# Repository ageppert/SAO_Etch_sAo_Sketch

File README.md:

# Etch sAo Sketch

The perfect pairing of an OLED Display, analog potentiometers, and a 3-axis accelerometer!

This is the primary repository for all things relevant to the Etch sAo Sketch.

Learn more about this project at: https://hackaday.io/project/197581-etch-sao-sketch

If you use the Arduino Demo code make sure it is configured for your hardware version (HWV) of the Etch sAo Sketch.

IMPORTANT ERRATA APPLIES TO ALL VERSIONS:

There is too much combined pull-up resistance with this board, the OLED board, the Hackaday Badge, and the Pico. This inhibits some I2C hardware implementations from working with the OLED display.

SOLUTION A: Firmware workaround is to use software I2C. See: https://github.com/ageppert/SAO_Etch_sAo_Sketch/pull/1

SOLUTION B: Hardware mods to remove interfering components. See: https://github.com/ageppert/SAO_Etch_sAo_Sketch/issues/8

-------------

# V1.3 - OLED VERSION - Hackaday Europe 2025 Elecrow version

This version was manufactured for Hackaday Europe 2025 by Elecrow and includes the Elecrow logo on the PCB below the screen. The files have been copied into this repository for easy reference, although it was in a more generic "SAO Sketch" repo for production. Hopefully you got a sticker from one of us to upgrade your SAO to "Etch sAo Sketch" when we were together in Berlin!

V1.3.1 FIXES: Removed I2C Pull-up Resistors R1/2 from the board.

-------------

# V1.2 - OLED VERSION - NOT BUILT

This version was an un-fabricated step in the development for Hackaday Europe 2025 with a separate repository located here: https://github.com/ageppert/SAO_Sketch. This version builds on V1.1 with some clean-up in the schematic and layout.

-------------

# V1.1 - OLED VERSION - Small batch to sell on Tindie

Refinements include:
1) Enable full range of the analog pots via the accelerometer's [reduced range] ADC inputs, with the option to still use analog signals on GPIO 1 and 2.
2) Use a taller male SAO header for easier connection to the main (red) PCBA.
3) Tweak alignment hole size/position for the alignment spheres and OLED position.

V1.1.1 FIXES: Removed I2C Pull-up Resistors R1/2 from the board.

Otherwise, it looks and functions just like V1.0.

-------------

# V1.0 - OLED VERSION - Shared at Hackaday Supercon.8 in 2024 and on Tindie

This version was shared at Hackaday Supercon.8 2024. It is available for purchase here: https://www.tindie.com/products/36383/

V1.0.1 FIXES: Removed I2C Pull-up Resistors R30/31 from the board.

V1.0 ERRATA: The full travel of the analog pots is only available through [analog] GPIO1&2 of the SAO port, and this works best when connected to analog pins of an MCU. My SAO DEMO CONTROLLER is a good host to use the V1.0 Etch sAo Sketch with. A reduced range of travel is available through the accelerometer ADC inputs via I2C. The included SAO Header pins need to be pushed back into the header body 1 mm so they extend far enough to be connected to the red PCBA after the OLED PCBA is stacked on the bottom.

The SAO DEMO CONTROLLER is available for purchase here: https://www.tindie.com/products/36033/

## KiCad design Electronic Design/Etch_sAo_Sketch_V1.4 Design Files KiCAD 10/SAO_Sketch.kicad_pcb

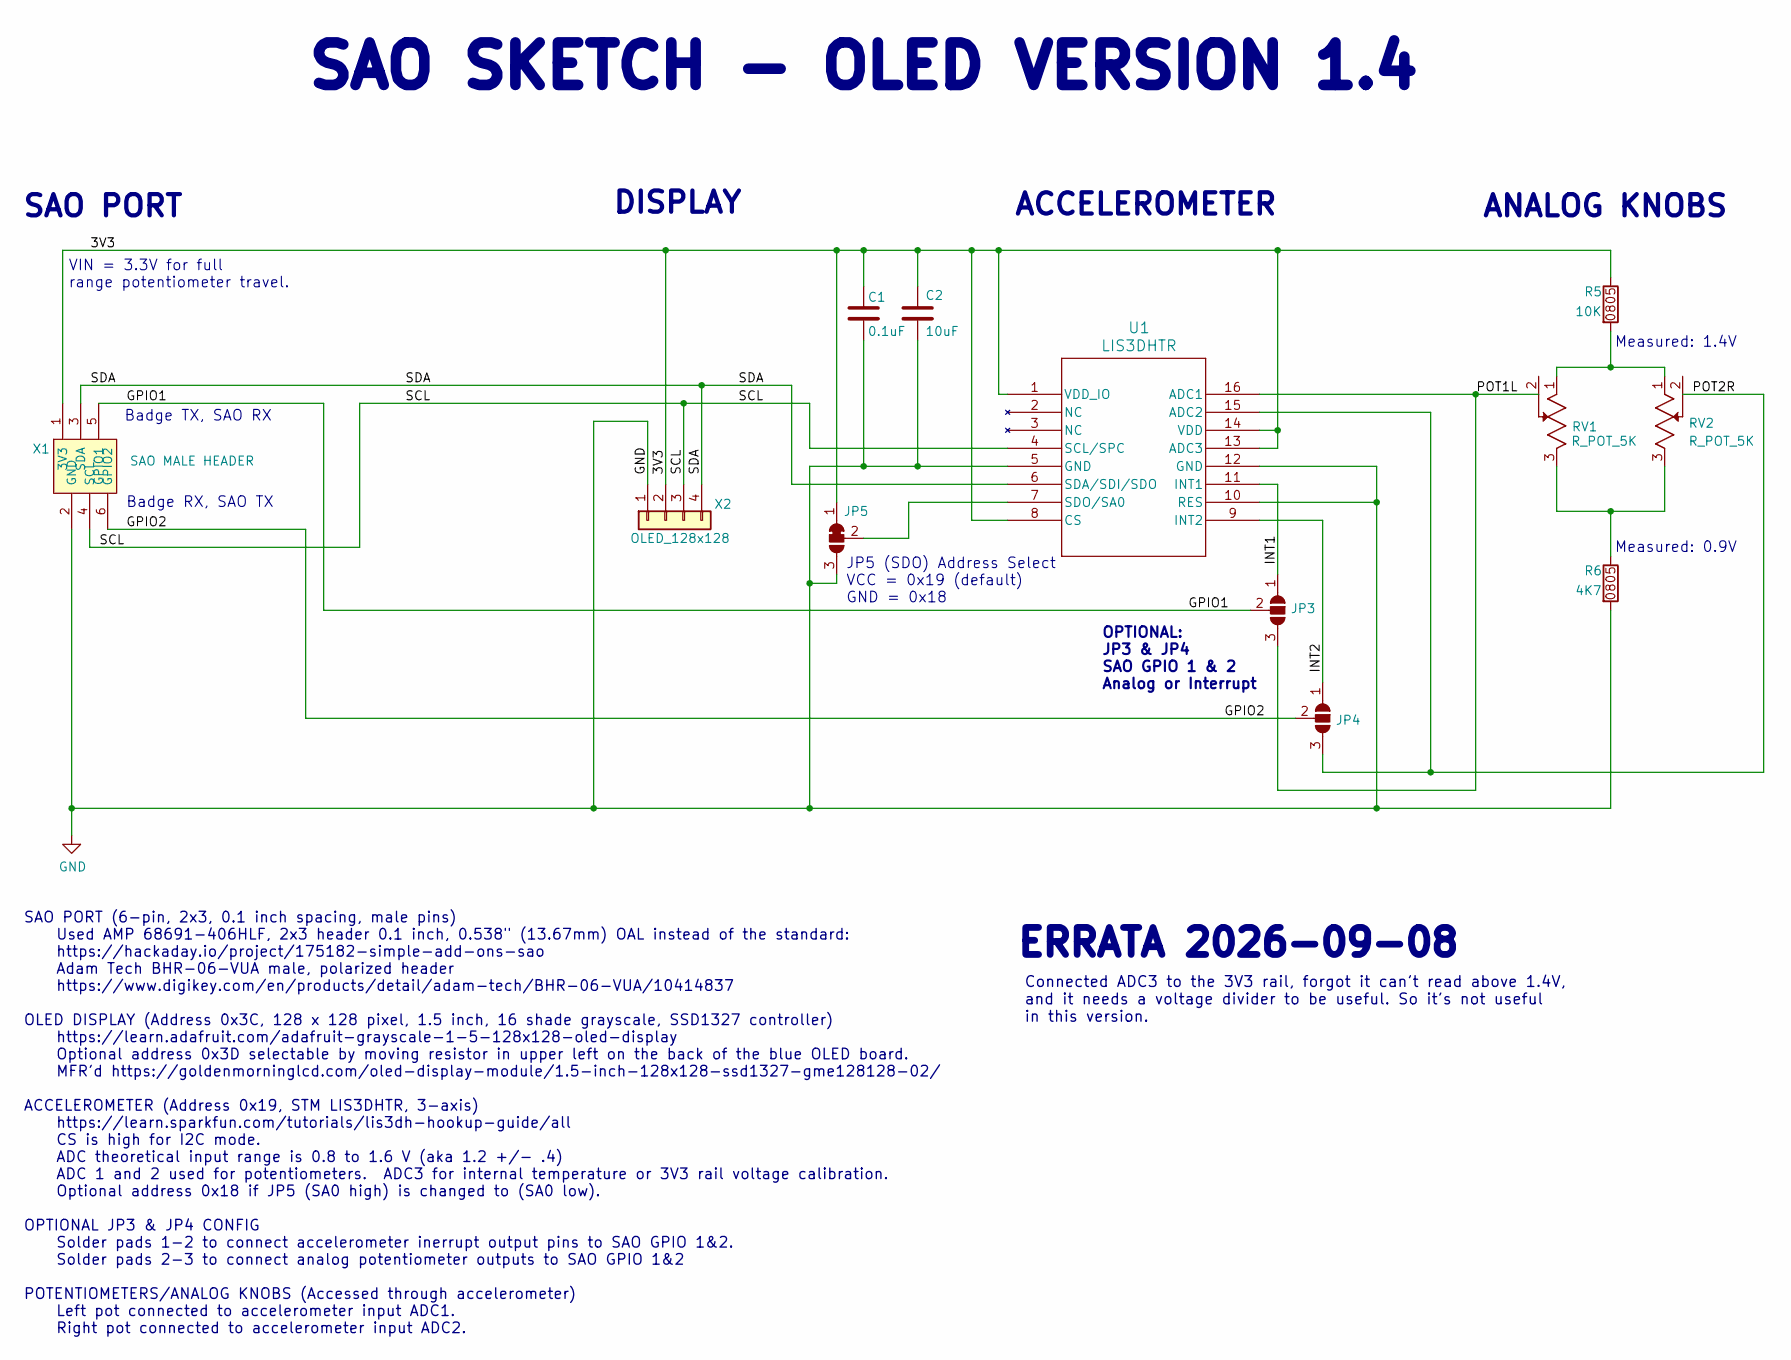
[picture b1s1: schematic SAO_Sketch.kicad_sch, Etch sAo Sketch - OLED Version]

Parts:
C1: 0.1uF; C_0805_2012Metric; LCSC C28233
C2: 10uF; C_0805_2012Metric; LCSC C15850
JP3, JP4: SolderJumper_3_Open; SolderJumper-3_P1.3mm_Open_RoundedPad1.0x1.5mm_NumberLabels
JP5: SolderJumper_3_Bridged12; SolderJumper-3_P1.3mm_Bridged12_RoundedPad1.0x1.5mm_NumberL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
R5: 10K; R_0805_2012Metric; LCSC C17414
R6: 4K7; R_0805_2012Metric; LCSC C17673
RV1, RV2: R_POT_5K; POT_RES3_91A_TTE; Manufacturer_Part_Number 91AR5KLF; Digi-Key_PN 987-1171-ND
U1: LIS3DHTR; LGA-16_3x3x1mm_STM; Manufacturer_Part_Number LIS3DHTR; Digi-Key_PN 497-10613-2-ND
X1: SAO MALE HEADER; Badgelife-SAOv169-BADGE-2x3-PINS-SHROUD-no-front-text; MPN 68691-406HLF; Digi-Key_PN 609-68691-406HLF-ND
X2: OLED_128x128; OLED_1.50_128x128

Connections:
/3V3: C1.1, C2.1, JP5.1 (A), R5.1, U1.1 (VDD_IO), U1.8 (CS), U1.13 (ADC3), U1.14 (VDD), X1.1 (3V3), X2.2
/GPIO1: JP3.2 (C), X1.5 (GPIO1)
/GPIO2: JP4.2 (C), X1.6 (GPIO2)
/INT1: JP3.1 (A), U1.11 (INT1)
/INT2: JP4.1 (A), U1.9 (INT2)
/POT1L: JP3.3 (B), RV1.2, U1.16 (ADC1)
/POT2R: JP4.3 (B), RV2.2, U1.15 (ADC2)
/SCL: U1.4 (SCL/SPC), X1.4 (SCL), X2.3
/SDA: U1.6 (SDA/SDI/SDO), X1.3 (SDA), X2.4
GND: C1.2, C2.2, JP5.3 (B), R6.2, U1.5 (GND), U1.10 (RES), U1.12 (GND), X1.2 (GND), X2.1
unnamed: JP5.2 (C), U1.7 (SDO/SA0)
unnamed: R5.2, RV1.1, RV2.1
unnamed: R6.1, RV1.3, RV2.3

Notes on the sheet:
Badge TX, SAO RX
SAO PORT (6-pin, 2x3, 0.1 inch spacing, male pins) Used AMP 68691-406HLF, 2x3 header 0.1 inch, 0.538" (13.67mm) OAL instead of the standard: https://hackaday.io/project/175182-simple-add-ons-sao Adam Tech BHR-06-VUA male, polarized header https://www.digikey.com/en/products/detail/adam-tech/BHR-06-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
Measured: 1.4V
DISPLAY
ANALOG KNOBS
SAO SKETCH - OLED VERSION 1.4
Measured: 0.9V
VIN = 3.3V for full range potentiometer travel.
JP5 (SDO) Address Select VCC = 0x19 (default) GND = 0x18
OPTIONAL: JP3 & JP4 SAO GPIO 1 & 2 Analog or Interrupt
Badge RX, SAO TX
Connected ADC3 to the 3V3 rail, forgot it can't read above 1.4V, and it needs a voltage divider to be useful. So it's not useful in this version.
ACCELEROMETER
SAO PORT
ERRATA 2026-09-08

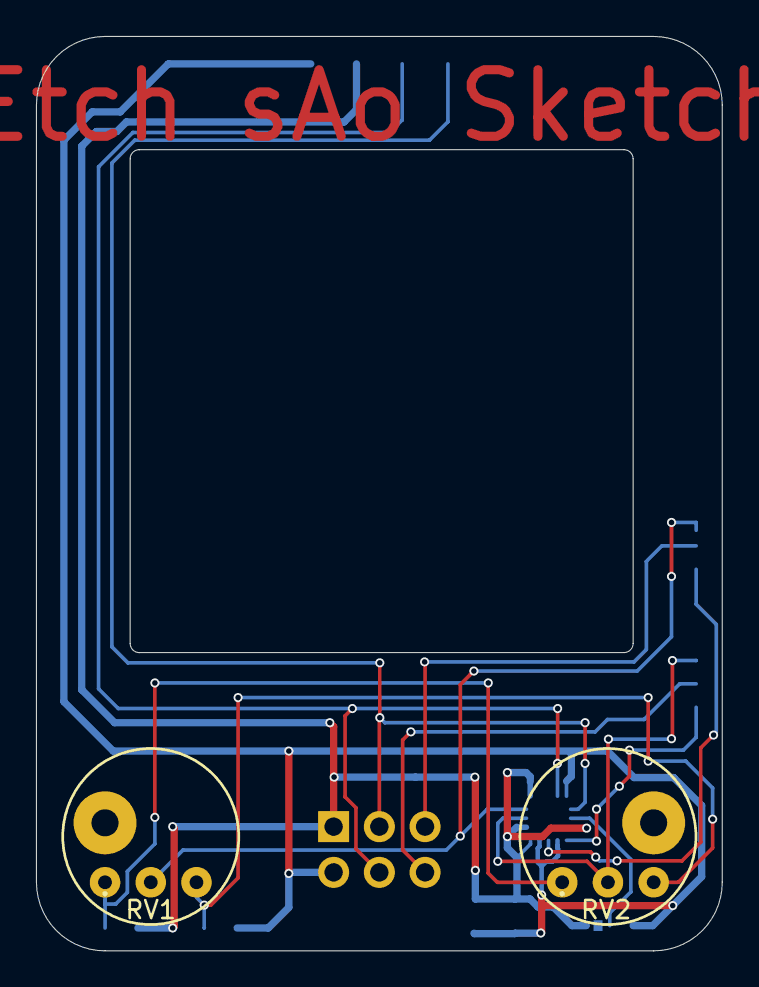
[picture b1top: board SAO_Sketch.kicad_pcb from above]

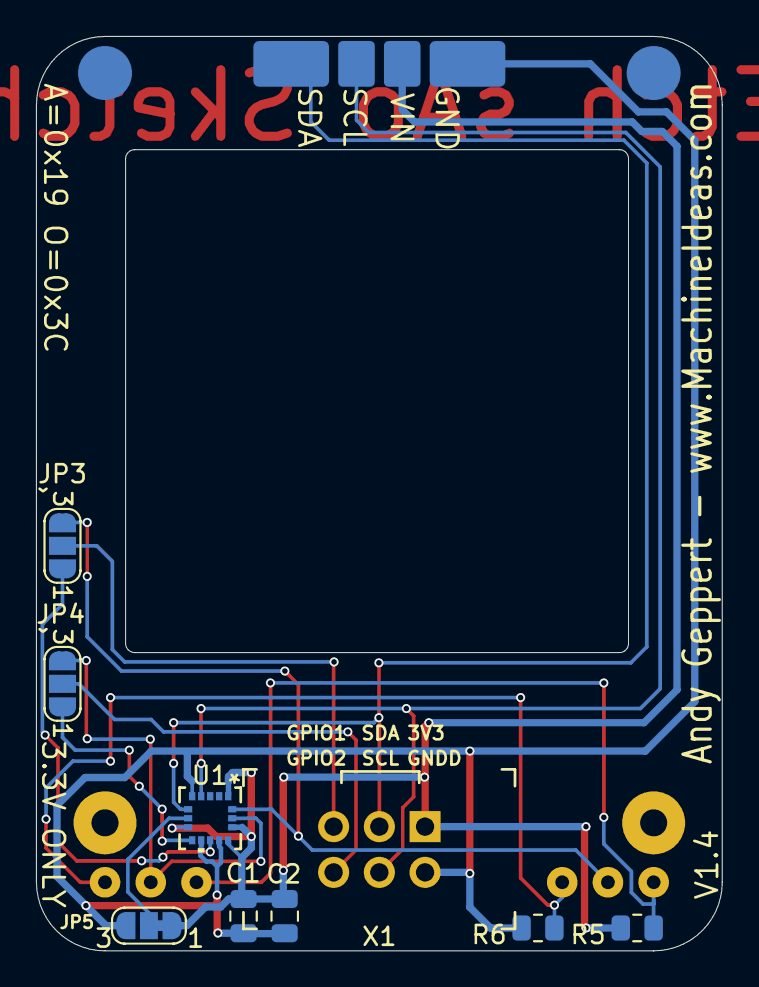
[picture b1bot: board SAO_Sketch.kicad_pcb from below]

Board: 2 copper layers, 38.1 x 50.8 mm, 12 parts (9 on the bottom side), 13 nets.

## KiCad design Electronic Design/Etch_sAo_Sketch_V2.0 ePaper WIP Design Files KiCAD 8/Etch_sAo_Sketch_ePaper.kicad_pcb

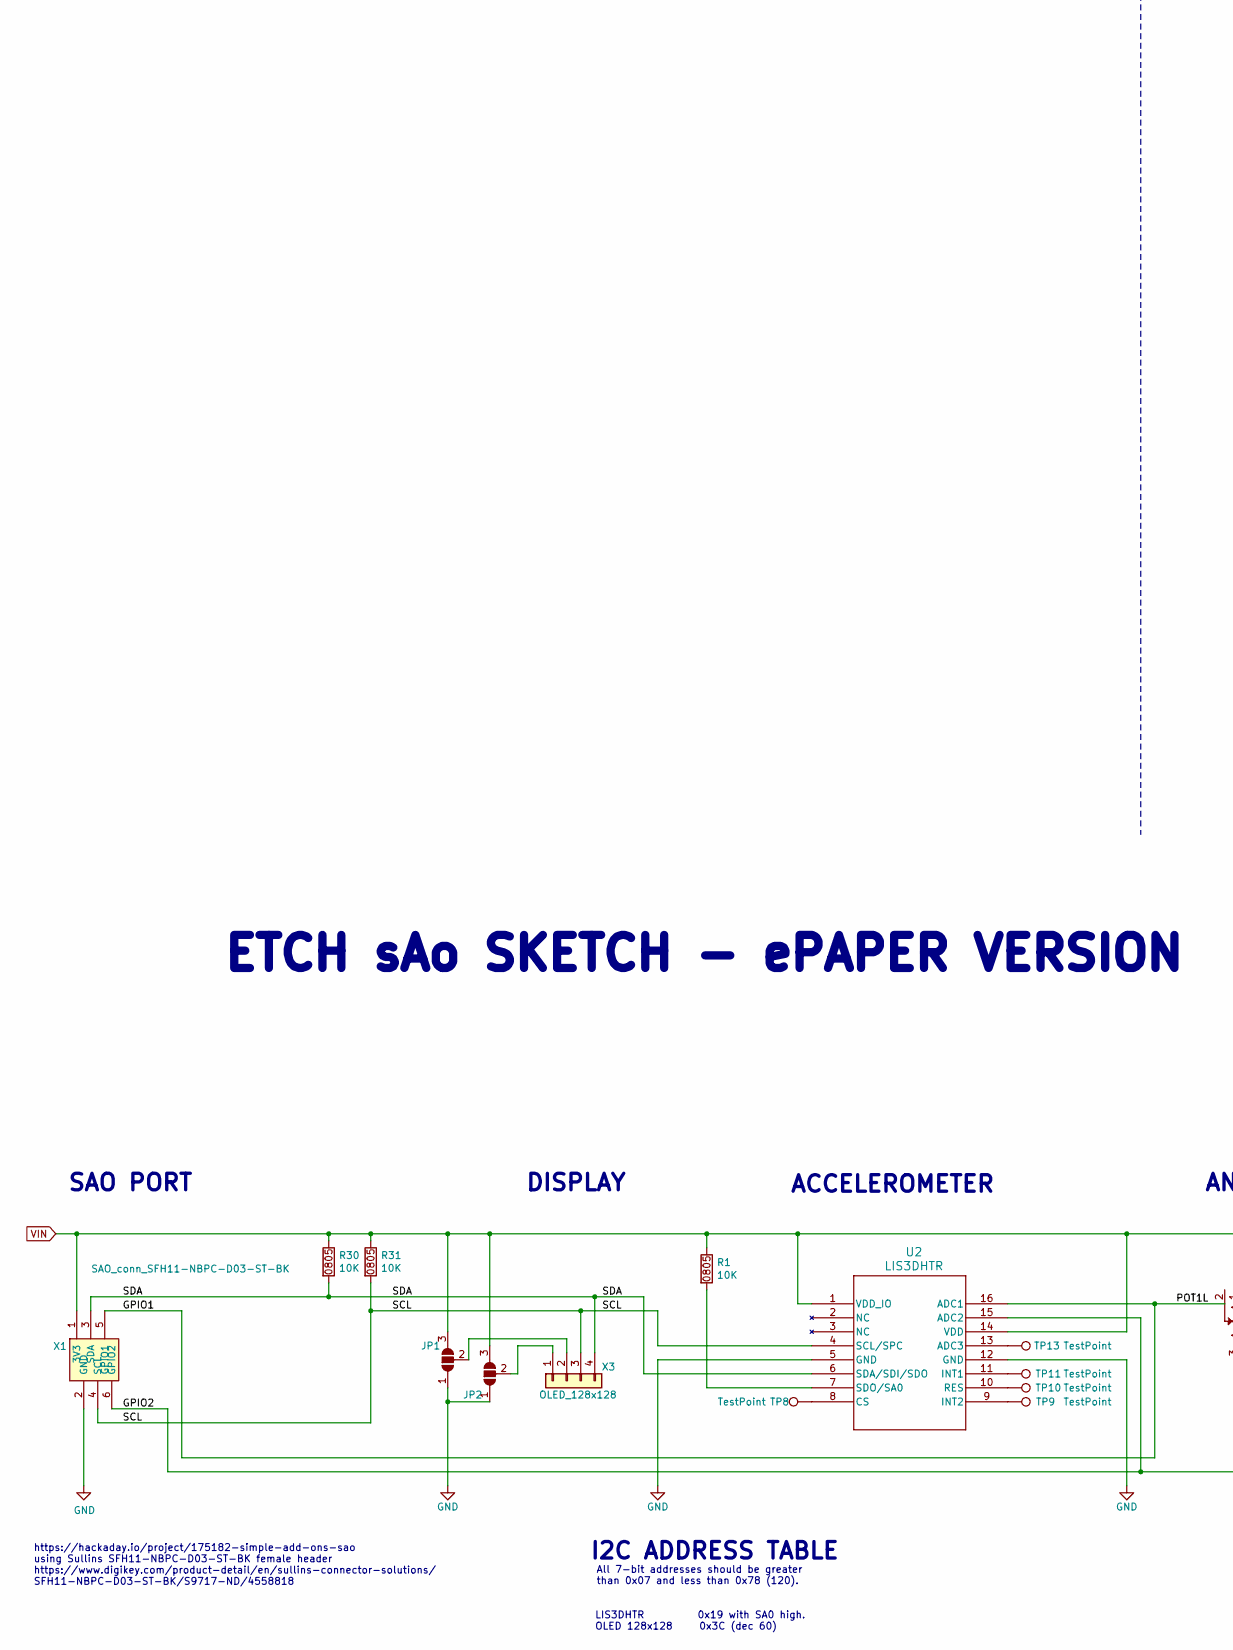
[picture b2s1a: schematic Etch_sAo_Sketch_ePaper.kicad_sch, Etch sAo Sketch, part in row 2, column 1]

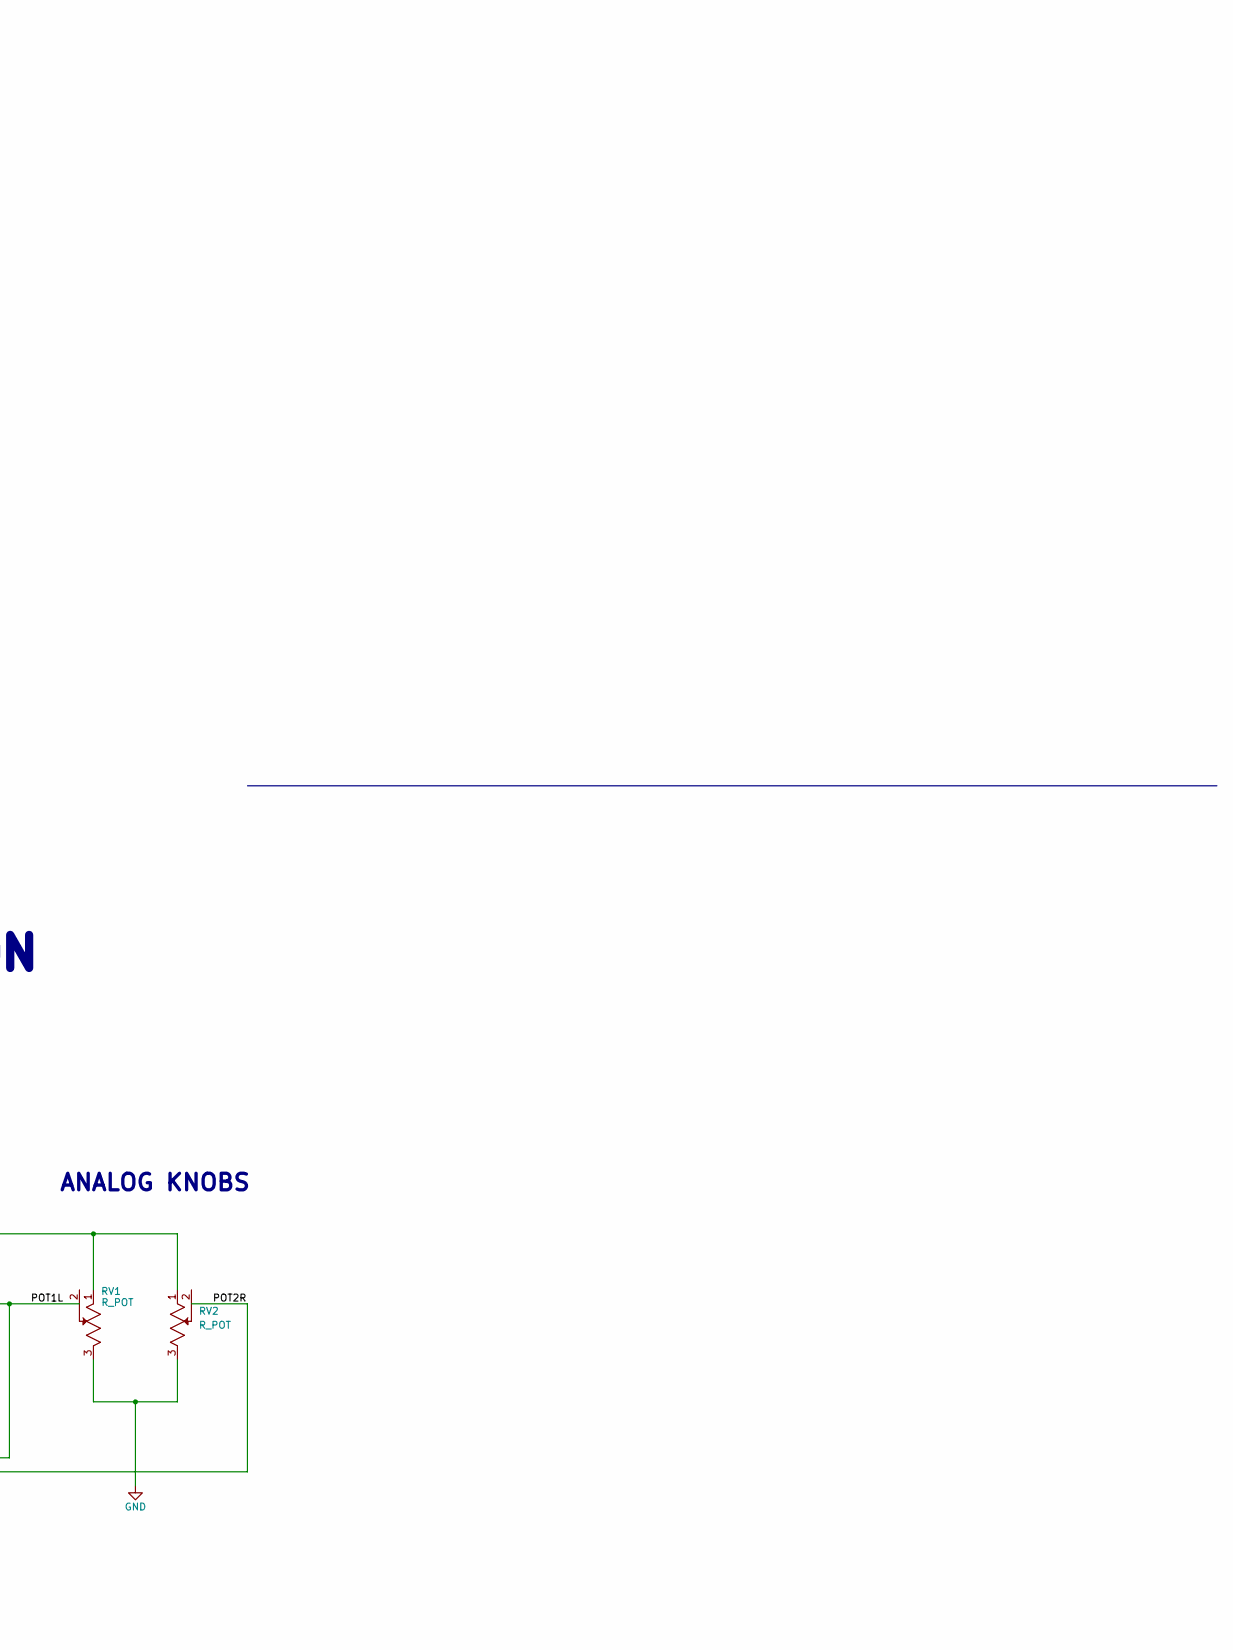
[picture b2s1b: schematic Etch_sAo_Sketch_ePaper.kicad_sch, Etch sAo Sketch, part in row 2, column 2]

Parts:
JP1, JP2: SolderJumper_3_Open; SolderJumper-3_P1.3mm_Open_RoundedPad1.0x1.5mm_NumberLabels
R1, R30, R31: 10K; R_0805_2012Metric; LCSC C17414
RV1, RV2: R_POT; POT_RES3_91A_TTE
TP8, TP9, TP10, TP11, TP13: TestPoint; TestPoint_Pad_1.0x1.0mm
U2: LIS3DHTR; LGA-16_3x3x1mm_STM; Manufacturer_Part_Number LIS3DHTR; Digi-Key_PN 497-10613-2-ND
X1: SAO_conn_SFH11-NBPC-D03-ST-BK; Badgelife-SAOv169-BADGE-2x3-Edge-Connect-no-front-text; MPN SFH11-NBPC-D03-ST-BK
X3: OLED_128x128; OLED_1.50_128x128

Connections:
/GPIO1: RV1.2, U2.16 (ADC1), X1.5 (GPIO1)
/GPIO2: RV2.2, U2.15 (ADC2), X1.6 (GPIO2)
/SCL: R31.2, U2.4 (SCL/SPC), X1.4 (SCL), X3.3
/SDA: R30.2, U2.6 (SDA/SDI/SDO), X1.3 (SDA), X3.4
GND: JP1.1 (A), JP2.1 (A), RV1.3, RV2.3, U2.5 (GND), U2.12 (GND), X1.2 (GND)
unnamed: JP1.2 (C), X3.2
unnamed: JP2.2 (C), X3.1
unnamed: TP13.1, U2.13 (ADC3)
unnamed: TP8.1, U2.8 (CS)
unnamed: TP11.1, U2.11 (INT1)
unnamed: TP9.1, U2.9 (INT2)
unnamed: TP10.1, U2.10 (RES)
unnamed: R1.2, U2.7 (SDO/SA0)
VIN: JP1.3 (B), JP2.3 (B), R1.1, R30.1, R31.1, RV1.1, RV2.1, U2.1 (VDD_IO), U2.14 (VDD), X1.1 (3V3)

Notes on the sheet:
https://hackaday.io/project/175182-simple-add-ons-sao using Sullins SFH11-NBPC-D03-ST-BK female header https://www.digikey.com/product-detail/en/sullins-connector-solutions/ SFH11-NBPC-D03-ST-BK/S9717-ND/4558818
LIS3DHTR 0x19 with SA0 high. OLED 128x128 0x3C (dec 60)
DISPLAY
ANALOG KNOBS
ETCH sAo SKETCH - ePAPER VERSION
I2C ADDRESS TABLE
ACCELEROMETER
All 7-bit addresses should be greater than 0x07 and less than 0x78 (120).
SAO PORT

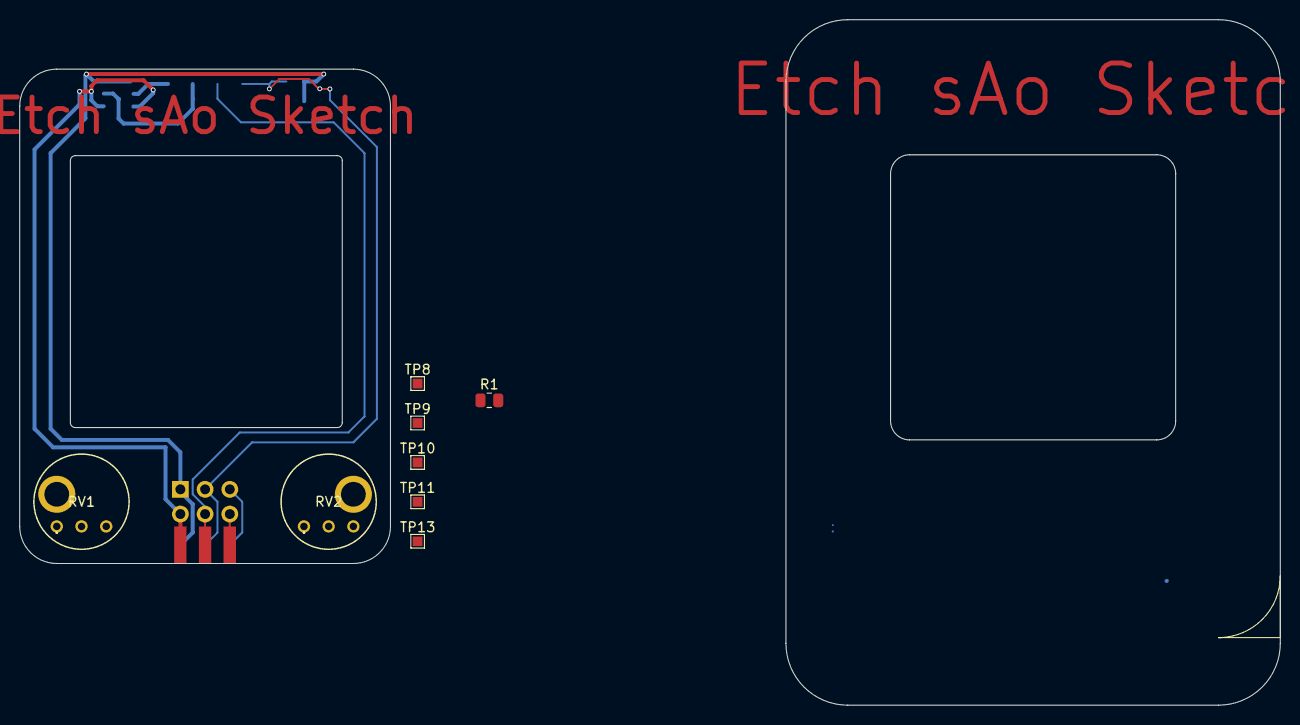
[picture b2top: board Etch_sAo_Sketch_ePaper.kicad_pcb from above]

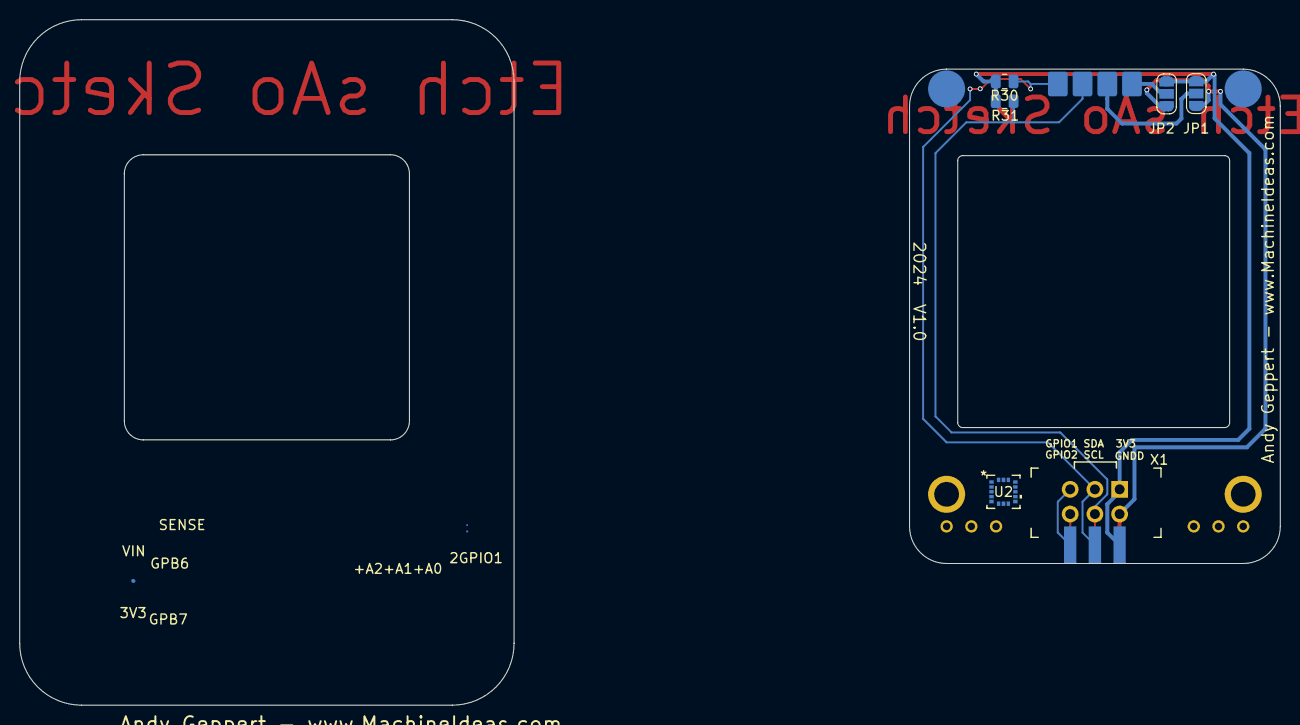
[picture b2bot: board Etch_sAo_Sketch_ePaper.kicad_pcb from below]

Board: 2 copper layers, 129.5 x 70.4 mm, 15 parts (6 on the bottom side), 14 nets.

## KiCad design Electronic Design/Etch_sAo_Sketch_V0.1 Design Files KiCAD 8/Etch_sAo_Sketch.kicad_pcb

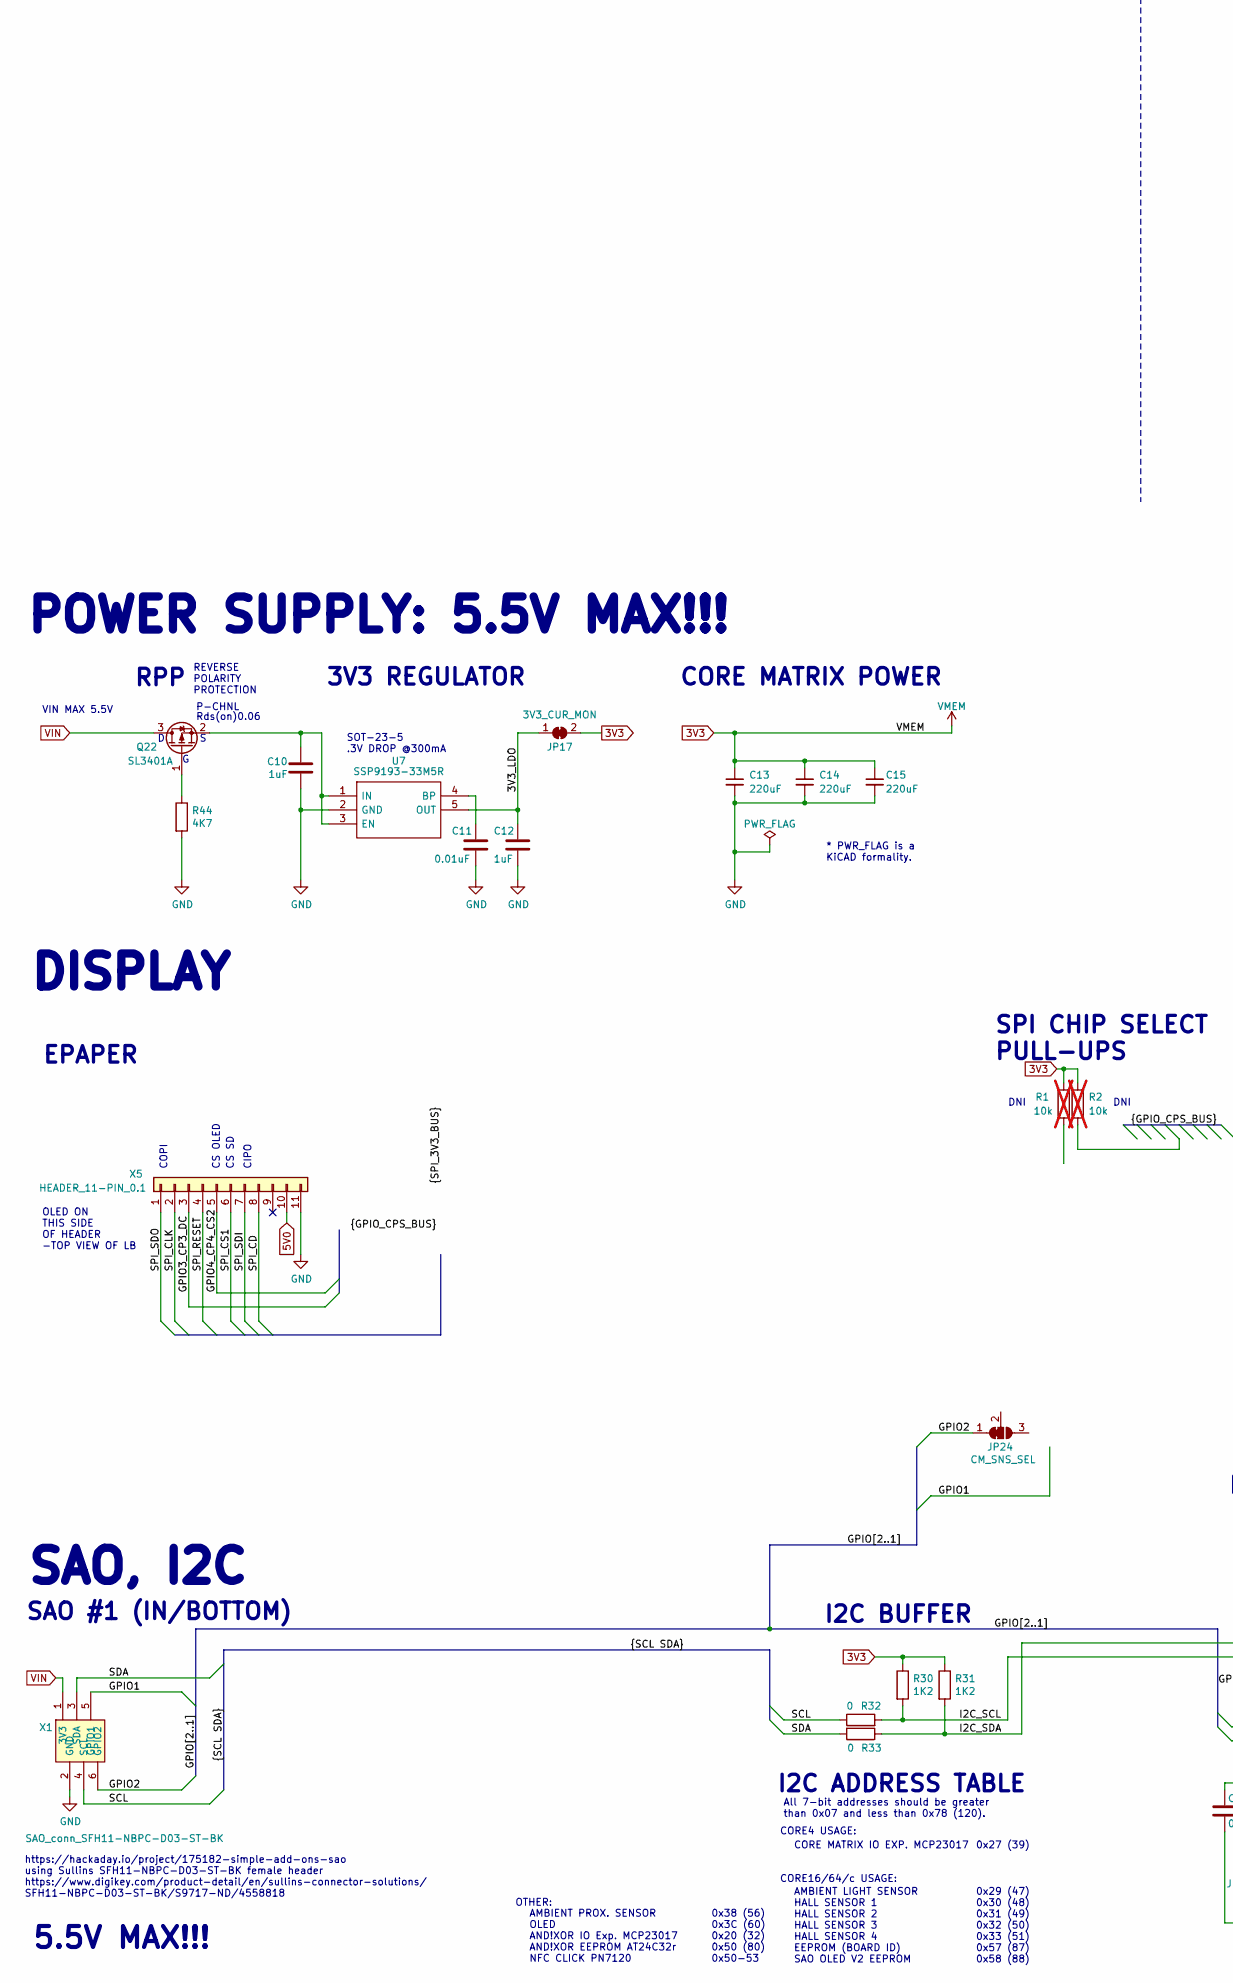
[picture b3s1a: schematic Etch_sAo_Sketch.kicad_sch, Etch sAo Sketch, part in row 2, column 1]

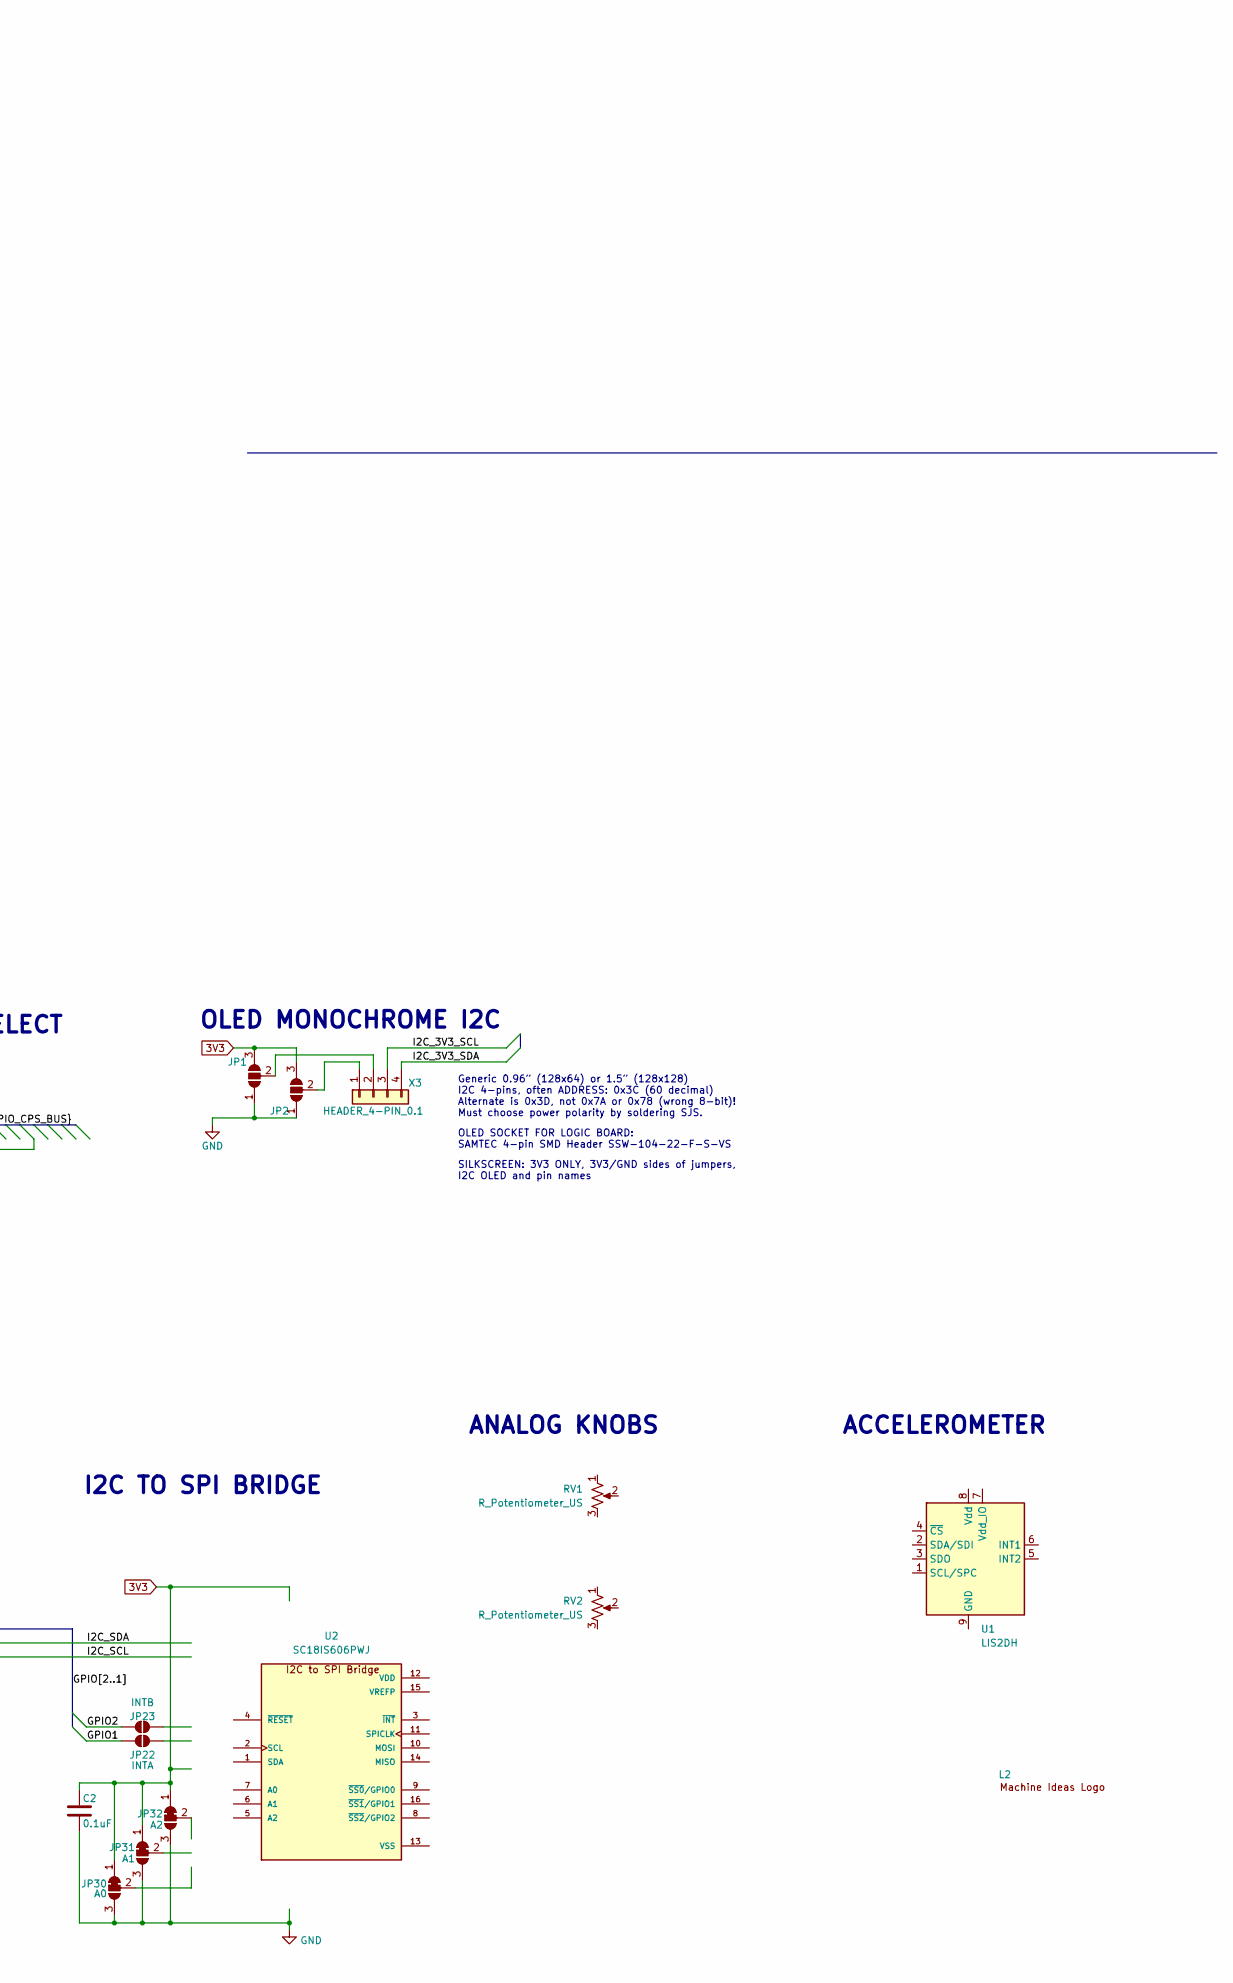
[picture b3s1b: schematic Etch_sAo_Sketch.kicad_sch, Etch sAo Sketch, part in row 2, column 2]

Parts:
C2: 0.1uF; C_0805_2012Metric; LCSC C28233
C10, C12: 1uF; C_0805_2012Metric; LCSC C28323
C11: 0.01uF; C_0805_2012Metric; LCSC C1710
C13, C14, C15: 220uF; C_1206_3216Metric; LCSC C412252
JP1, JP2: SolderJumper_3_Open; SolderJumper-3_P1.3mm_Open_RoundedPad1.0x1.5mm_NumberLabels
JP17: 3V3_CUR_MON; SolderJumper-2_P1.3mm_Bridged_RoundedPad1.0x1.5mm
JP22: INTA; SolderJumper-2_P1.3mm_Open_Pad1.0x1.5mm
JP23: INTB; SolderJumper-2_P1.3mm_Open_Pad1.0x1.5mm
JP24: CM_SNS_SEL; SolderJumper-3_P1.3mm_Bridged12_Pad1.0x1.5mm
JP30: A0; SolderJumper-3_P1.3mm_Bridged12_Pad1.0x1.5mm
JP31: A1; SolderJumper-3_P1.3mm_Bridged12_Pad1.0x1.5mm
JP32: A2; SolderJumper-3_P1.3mm_Bridged12_Pad1.0x1.5mm
L2: Machine_Ideas_logo
Q22: SL3401A; SOT-23-3; MPN SL3401A-TP; LCSC C350311
R1, R2: 10k; R_0805_2012Metric; LCSC C17414; not fitted
R30, R31: 1K2; R_0805_2012Metric; LCSC C17379
R32, R33: 0; R_0805_2012Metric; LCSC C17477
R44: 4K7; R_0805_2012Metric; LCSC C17673
RV1, RV2: R_Potentiometer_US; Potentiometer_Alps_RK09L_Single_Vertical
U1: LIS2DH; LGA-14_2x2mm_P0.35mm_LayoutBorder3x4y
U2: SC18IS606PWJ; SOP65P640X110-16N; PARTREV 1.0
U7: SSP9193-33M5R; SOT-23-5; Manufacturer_Part_Number SGM2007-3.3XN5/TR; Mouser Part Number SGM2007-3.3XN5/TR
X1: SAO_conn_SFH11-NBPC-D03-ST-BK; Badgelife-SAOv169-BADGE-2x3-no-front-text; MPN SFH11-NBPC-D03-ST-BK
X3: HEADER_4-PIN_0.1; PinSocket_1x04_P2.54mm_Vertical
X5: HEADER_11-PIN_0.1; PinSocket_1x11_P2.54mm_Vertical

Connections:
3V3: C2.1, C13.1, C14.1, C15.1, JP1.3 (B), JP2.3 (B), JP17.2 (B), JP30.1 (A), JP31.1 (A), JP32.1 (A), R1.1, R2.2, R30.1, R31.1
5V0: X5.10
/3V3_LDO: C12.1, JP17.1 (A), U7.5 (OUT)
/GPIO1: JP22.1 (A), X1.5 (GPIO1)
/GPIO2: JP23.1 (A), JP24.1 (A), X1.6 (GPIO2)
/GPIO3_CP3_DC: X5.3
/GPIO4_CP4_CS2: X5.5
/I2C_3V3_SCL: X3.3
/I2C_3V3_SDA: X3.4
/I2C_SCL: R30.2, R32.2
/I2C_SDA: R31.2, R33.1
/SCL: R32.1, X1.4 (SCL)
/SDA: R33.2, X1.3 (SDA)
/SPI_CD: X5.8
/SPI_CLK: X5.2
/SPI_CS1: X5.6
/SPI_RESET: X5.4
/SPI_SDI: X5.7
/SPI_SDO: X5.1
GND: C2.2, C10.2, C11.2, C12.2, C13.2, C14.2, C15.2, JP1.1 (A), JP2.1 (A), JP30.3 (B), JP31.3 (B), JP32.3 (B), R44.2, U7.2 (GND), X1.2 (GND), X5.11
unnamed: JP1.2 (C), X3.2
unnamed: JP2.2 (C), X3.1
unnamed: Q22.1 (G), R44.1
unnamed: C10.1, Q22.2 (S), U7.1 (IN), U7.3 (EN)
unnamed: U1.9 (GND), U1.10 (GND), U1.11 (GND), U1.12 (GND), U1.13 (GND), U1.14 (GND)
unnamed: C11.1, U7.4 (BP)
VIN: Q22.3 (D), X1.1 (3V3)

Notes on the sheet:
OLED MONOCHROME I2C
AMBIENT PROX. SENSOR OLED AND!XOR IO Exp. MCP23017 AND!XOR EEPROM AT24C32r NFC CLICK PN7120
SILKSCREEN: 3V3 ONLY, 3V3/GND sides of jumpers, I2C OLED and pin names
https://hackaday.io/project/175182-simple-add-ons-sao using Sullins SFH11-NBPC-D03-ST-BK female header https://www.digikey.com/product-detail/en/sullins-connector-solutions/ SFH11-NBPC-D03-ST-BK/S9717-ND/4558818
CS SD
EPAPER
OLED SOCKET FOR LOGIC BOARD: SAMTEC 4-pin SMD Header SSW-104-22-F-S-VS
CORE4 USAGE:
CORE MATRIX IO EXP. MCP23017
SOT-23-5 .3V DROP @300mA
0x29 (47) 0x30 (48) 0x31 (49) 0x32 (50) 0x33 (51) 0x57 (87) 0x58 (88)
CIPO
* PWR_FLAG is a KiCAD formality.
I2C TO SPI BRIDGE
AMBIENT LIGHT SENSOR HALL SENSOR 1 HALL SENSOR 2 HALL SENSOR 3 HALL SENSOR 4 EEPROM (BOARD ID) SAO OLED V2 EEPROM
POWER SUPPLY: 5.5V MAX!!!
DNI
Rds(on)0.06
5.5V MAX!!!
3V3 REGULATOR
ANALOG KNOBS
VIN MAX 5.5V
0x38 (56) 0x3C (60) 0x20 (32) 0x50 (80) 0x50-53
SAO #1 (IN/BOTTOM)
0x27 (39)
OLED ON THIS SIDE OF HEADER -TOP VIEW OF LB
OTHER:
COPI
REVERSE POLARITY PROTECTION
I2C BUFFER
I2C ADDRESS TABLE
SAO, I2C
SPI CHIP SELECT PULL-UPS
CORE16/64/c USAGE:
RPP
DISPLAY
ACCELEROMETER
CORE MATRIX POWER
P-CHNL
All 7-bit addresses should be greater than 0x07 and less than 0x78 (120).

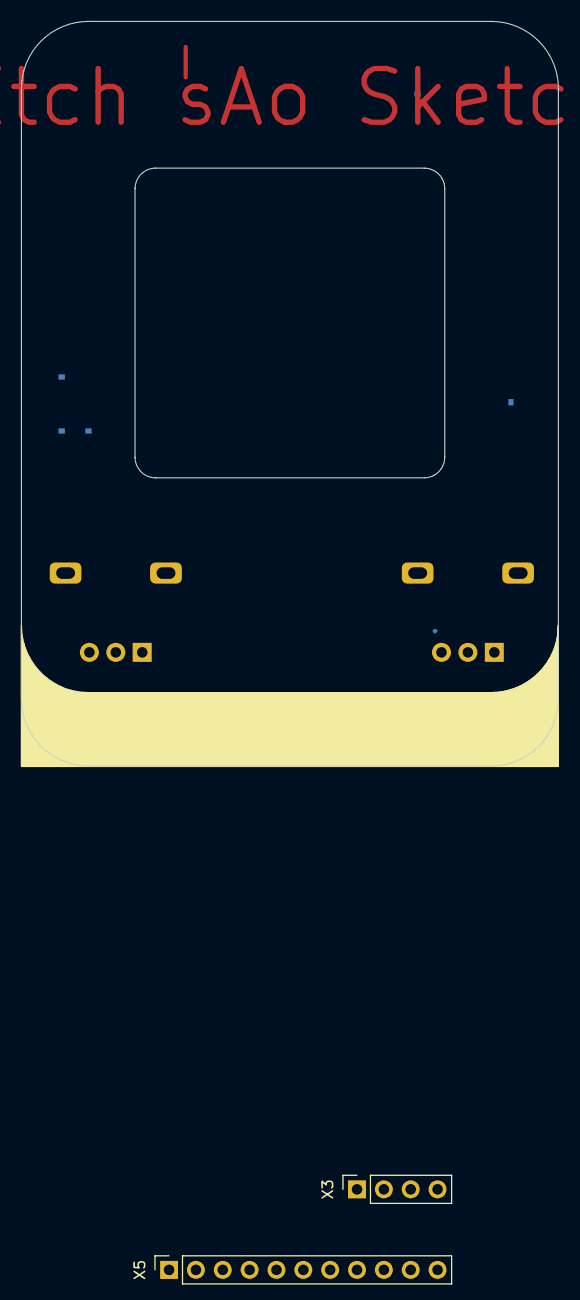
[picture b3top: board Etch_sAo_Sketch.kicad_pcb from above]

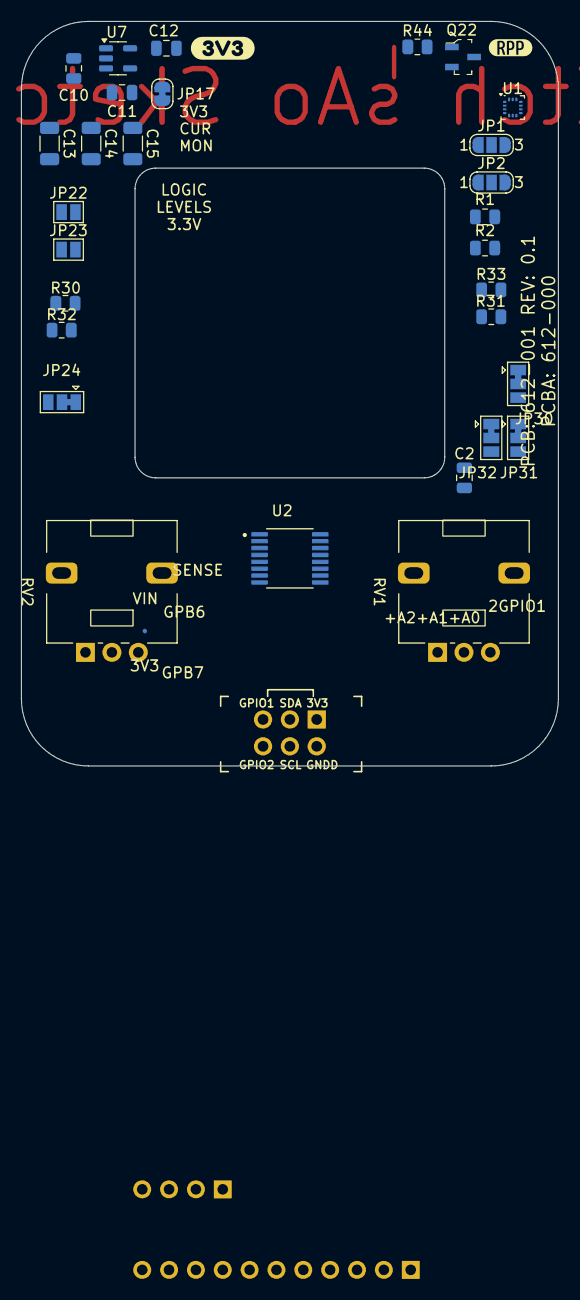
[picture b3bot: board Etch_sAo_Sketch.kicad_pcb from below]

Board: 2 copper layers, 50.8 x 70.4 mm, 35 parts (32 on the bottom side), 16 nets.

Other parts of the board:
kibuzzard-66C5FD67: G***; kibuzzard-66C5FD67
kibuzzard-6417AF30: G***; kibuzzard-6417AF30
